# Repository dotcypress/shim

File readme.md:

# SHIM

Tiny ARM Cortex-M0+ Development/Prototyping board.

## Features

- USB VBUS, ext. VIN, ext. 5V, ext +3.3V 
- Push-buttons: User and Reset 
- LEDs: Power, 2 User LEDs
- Connectors: 2 GPIO, 4 PWM, 1 SWD
- Breadboard friendly

## Resources

- [Schematics](docs/schematics.pdf)
- [Gerber files](docs/fabrication.zip)
- [BOM](docs/bom.csv)
- [KiCad project](kicad/)
- [Rust firmware for 4-DOF robotic arm toy](src/)

## License

Licensed under either of

- Apache License, Version 2.0 ([LICENSE-APACHE](LICENSE-APACHE) or
  http://www.apache.org/licenses/LICENSE-2.0)
- MIT license ([LICENSE-MIT](LICENSE-MIT) or http://opensource.org/licenses/MIT)

at your option.

### Contribution

Unless you explicitly state otherwise, any contribution intentionally submitted
for inclusion in the work by you, as defined in the Apache-2.0 license, shall be
dual licensed as above, without any additional terms or conditions.

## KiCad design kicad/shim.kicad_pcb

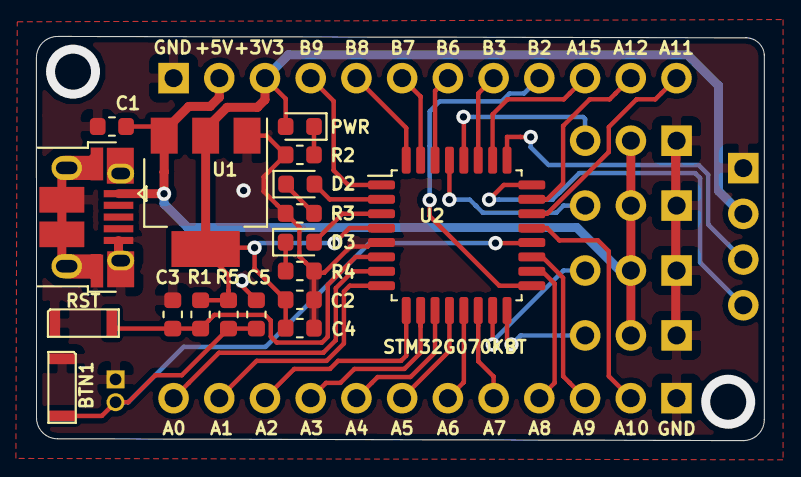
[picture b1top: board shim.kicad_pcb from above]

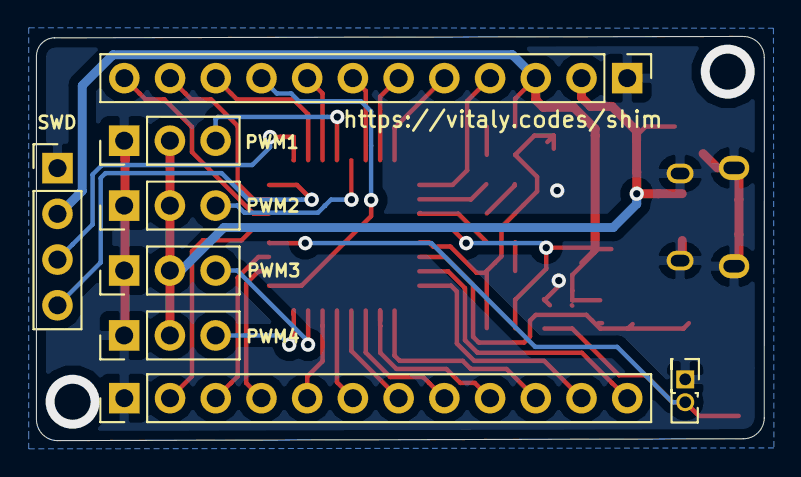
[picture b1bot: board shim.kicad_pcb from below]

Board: 2 copper layers, 40.4 x 22.5 mm, 26 parts (8 on the bottom side), 34 nets.

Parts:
C1, C3, C4, C5: 100nF; C_0603_1608Metric
C2: 10uF; C_0603_1608Metric
D1: PWR; LED_0603_1608Metric
D2: LD1; LED_0603_1608Metric
D3: LD2; LED_0603_1608Metric
J1: USB_B_Micro; USB_Micro-B_Amphenol_10103594-0001LF_Horizontal
J2: PORT1; PinHeader_1x12_P2.54mm_Vertical
J3: PORT2; PinHeader_1x12_P2.54mm_Vertical
J4: SWD; PinHeader_1x04_P2.54mm_Vertical
J5: PWM1; PinHeader_1x03_P2.54mm_Vertical
J6: PWM2; PinHeader_1x03_P2.54mm_Vertical
J7: PWM3; PinHeader_1x03_P2.54mm_Vertical
J8: PWM4; PinHeader_1x03_P2.54mm_Vertical
J9: Button; PinHeader_2x01_P1.27mm_Vertical
R1, R5: 10K; R_0603_1608Metric
R2, R3, R4: 330R; R_0603_1608Metric
SW1: RST; SW
SW2: BTN1; SW
U1: LD1117S33TR; SOT-223-3_TabPin2
U2: STM32G070KBT; LQFP-32_7x7mm_P0.8mm

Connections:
+3V3: C2.1, C4.1, D1.2, J3.3, J4.2, R1.1, R5.1, U1.2, U2.4
+5V: C1.1, J1.1, J3.2, J5.2, J6.2, J7.2, J8.2, U1.3
/A0: J2.12, U2.7
/A1: J2.11, U2.8
/A2: J2.10, U2.9
/A3: J2.9, U2.10
/A4: J2.8, U2.11
/A5: J2.7, U2.12
/A8: J2.4, U2.18
/A9: J2.3, U2.19
/A10: J2.2, U2.21
/A11: J3.12, U2.22
/A12: J3.11, U2.23
/A15: J3.10, U2.26
/B2: J3.9, U2.17
/B3: J3.8, U2.27
/B6: J3.7, U2.30
/B7: J3.6, U2.31
/B8: J3.5, U2.32
/B9: J3.4, U2.1
/BTN1: C5.2, J9.2, R5.2, SW2.2, U2.20
/LED1: D2.2, U2.2
/LED2: D3.2, U2.3
/PWM1: J5.3, U2.28
/PWM2: J6.3, U2.29
/PWM3: J7.3, U2.15
/PWM4: J8.3, U2.16
/RST: C3.2, R1.2, SW1.2, U2.6
/SWDCLK: J4.3, U2.25
/SWDIO: J4.4, U2.24
GND: C1.2, C2.2, C3.1, C4.2, C5.1, J1.5, J1.6, J2.1, J3.1, J4.1, J5.1, J6.1, J7.1, J8.1, J9.1, R2.1, R3.1, R4.1, SW1.1, SW2.1, U1.1, U2.5
unnamed: D1.1, R2.2
unnamed: D2.1, R3.2
unnamed: D3.1, R4.2

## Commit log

2019-07-23 update BOM
2019-07-23 add pcb photo
2019-07-23 tuning
2019-07-29 update openocd config
